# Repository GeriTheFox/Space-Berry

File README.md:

# Space-Berry
 AMD / Xilinx Zynq Ultrascale+ based SBC

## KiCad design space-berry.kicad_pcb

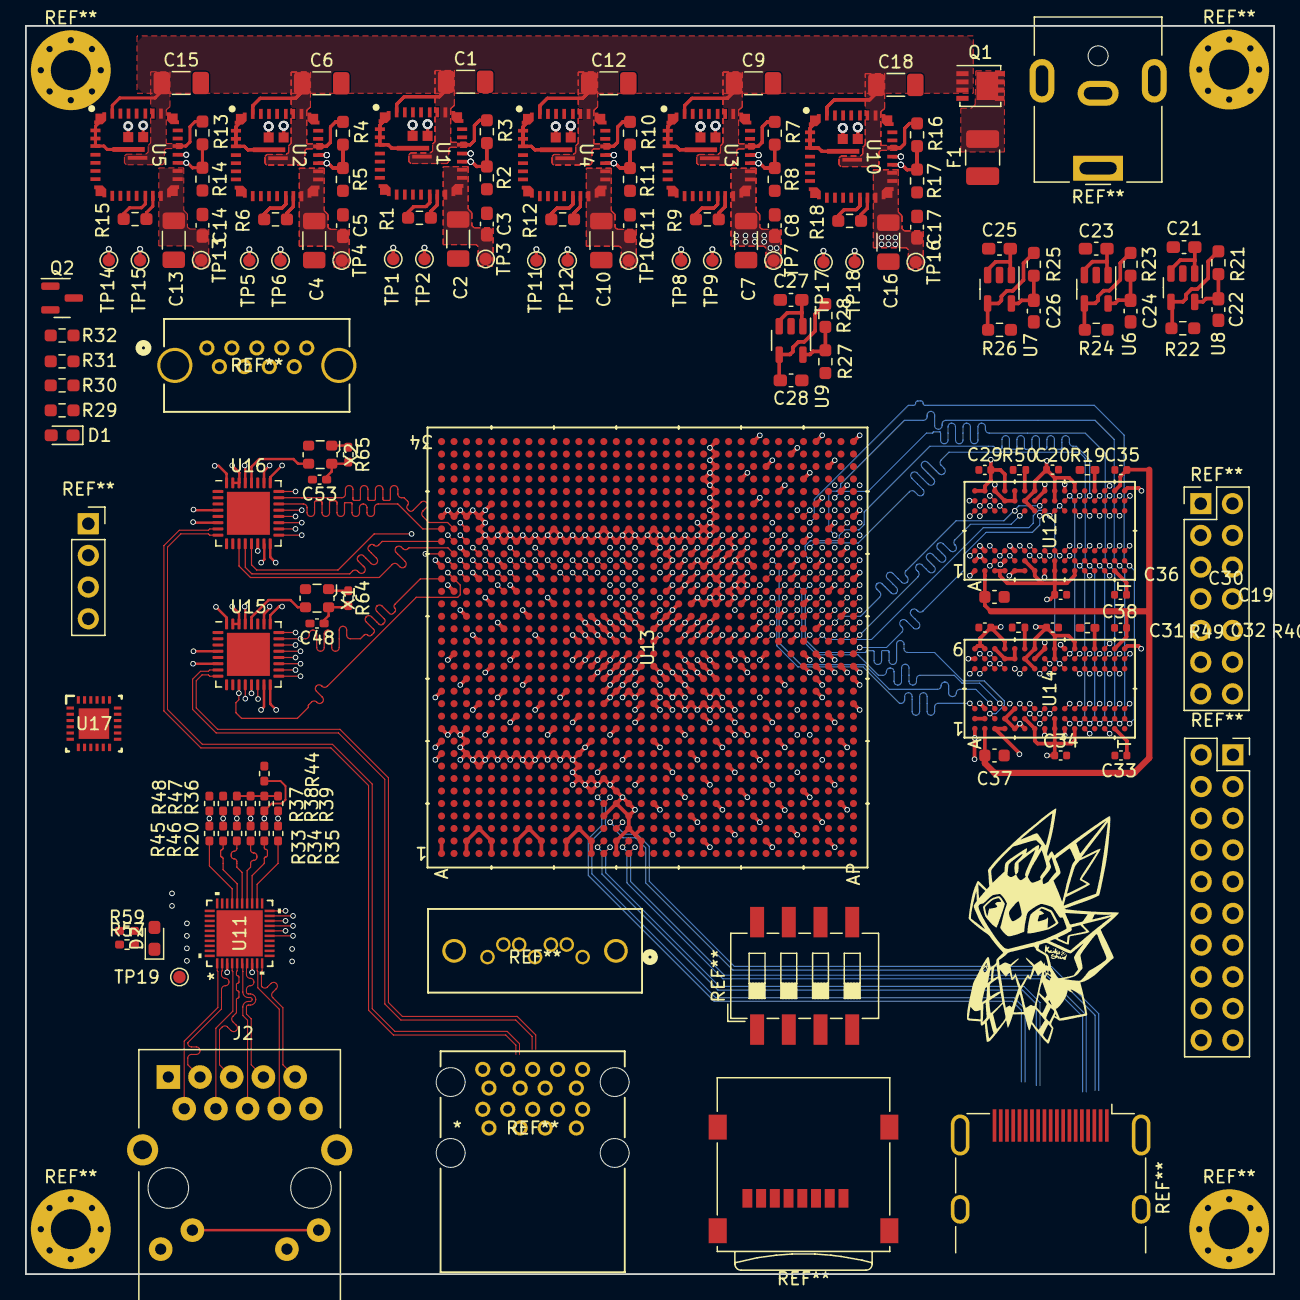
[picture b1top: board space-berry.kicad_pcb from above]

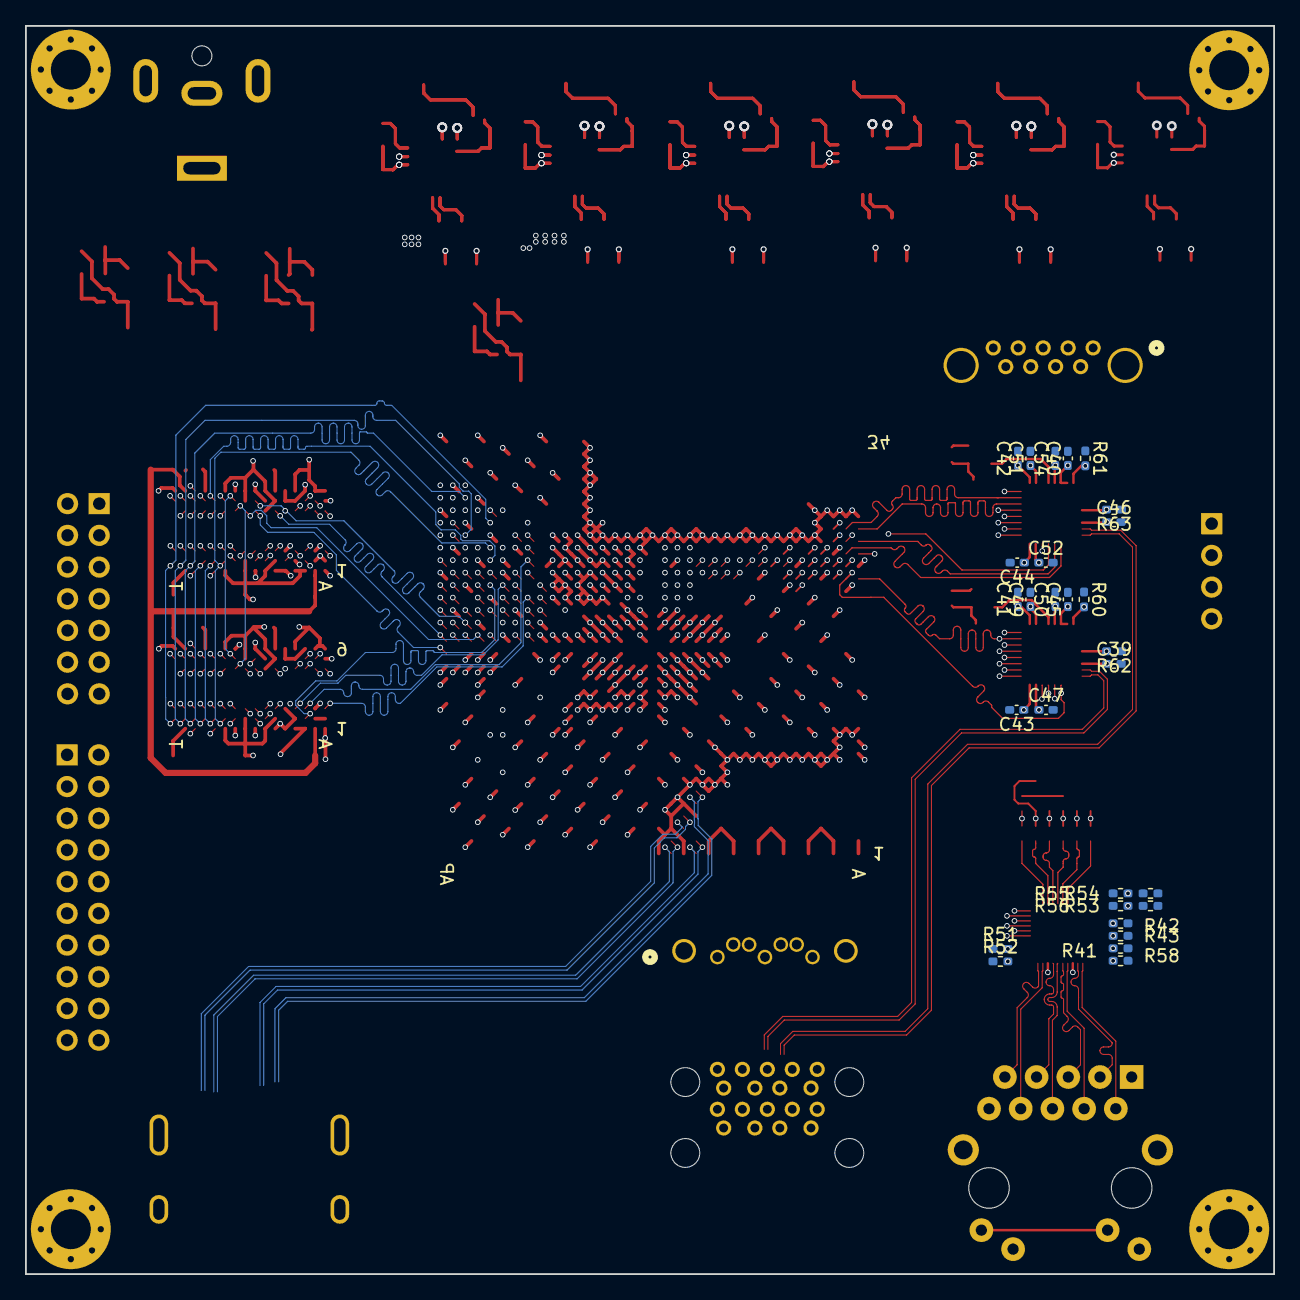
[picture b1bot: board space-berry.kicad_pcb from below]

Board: 8 copper layers, 100.0 x 100.0 mm, 163 parts (28 on the bottom side), 228 nets.

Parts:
C1, C6, C9, C12, C15, C18: 20uF; C_1206_3216Metric_Pad1.33x1.80mm_HandSolder
C2, C4, C7, C10, C13, C16: 44uF; C_1206_3216Metric_Pad1.33x1.80mm_HandSolder
C3, C5, C8, C11, C14, C17: 100nF; C_0603_1608Metric_Pad1.08x0.95mm_HandSolder
C19, C20, C29, C30, C31, C32, C33, C34, C35, C38: 100nF; C_0402_1005Metric
C21, C22, C23, C24, C25, C26, C27, C28: 10uf; C_0603_1608Metric_Pad1.08x0.95mm_HandSolder
C36, C37: 4.7uF; C_0603_1608Metric
C39, C40, C41, C42, C43, C44, C45, C46, C47, C48, C49, C50, C51, C52, C53, C54: 100nF; C_0402_1005Metric_Pad0.74x0.62mm_HandSolder
D1, D2: LED; LED_0603_1608Metric_Pad1.05x0.95mm_HandSolder
F1: Fuse; Fuse_1210_3225Metric_Pad1.42x2.65mm_HandSolder
J2: RJ45_RB1-125B8G1A; RJ45_UDE_RB1-125B8G1A
Q1: SiS415DNT; Vishay_PowerPAK_1212-8_Single
Q2: TSM2302CX; SOT-23
R1, R6, R9, R12, R15, R18: R adj; R_0603_1608Metric_Pad0.98x0.95mm_HandSolder
R2, R5, R8, R11, R14, R17: 20K opt; R_0603_1608Metric_Pad0.98x0.95mm_HandSolder
R3, R4, R7, R10, R13, R16: 1k opt; R_0603_1608Metric_Pad0.98x0.95mm_HandSolder
R19, R40: 499; R_0402_1005Metric_Pad0.72x0.64mm_HandSolder
R20, R33, R34, R35, R41, R42, R43, R45, R46, R51: 22; R_0402_1005Metric_Pad0.72x0.64mm_HandSolder
R21, R22, R23, R24, R25, R26, R27, R28: R; R_0603_1608Metric_Pad0.98x0.95mm_HandSolder
R29: 10; R_0603_1608Metric_Pad0.98x0.95mm_HandSolder
R30, R31, R32: 10K; R_0603_1608Metric_Pad0.98x0.95mm_HandSolder
R36, R37, R38, R39, R52, R55, R56, R59: 4K7; R_0402_1005Metric_Pad0.72x0.64mm_HandSolder
R44, R47, R48: 1K; R_0402_1005Metric_Pad0.72x0.64mm_HandSolder
R49, R50: 240; R_0402_1005Metric
R53, R54, R57: 420; R_0402_1005Metric_Pad0.72x0.64mm_HandSolder
R58: 2K5; R_0402_1005Metric_Pad0.72x0.64mm_HandSolder
R60, R61, R62, R63, R64, R65: R; R_0402_1005Metric_Pad0.72x0.64mm_HandSolder
TP1, TP5, TP8, TP11, TP14, TP17: PG; TestPoint_Pad_D1.0mm
TP2, TP6, TP9, TP12, TP15, TP18: EN; TestPoint_Pad_D1.0mm
TP3, TP4, TP7, TP10, TP13, TP16: Vout; TestPoint_Pad_D1.0mm
TP19: Eth clk; TestPoint_Pad_D1.0mm
U1, U2, U3, U4, U5, U10: NAM12S06-D
U6, U7, U8, U9: TLV75801PDBV; SOT-23-5
U11: RTL8211F-CG; RTL8211F-CG_RTK
U12, U14: K4A8G165WC-BCTD; FBGA96X16_7P5X13P3_SAM
U13: XCZU15EG-2FFVB1156E; FFVB1156_XIL
U15, U16: USB3300-EZK; QFN-32-1EP_5x5mm_P0.5mm_EP3.45x3.45mm
U17: CDCI6214RGET; CDCI6214RGET_NV
X1, X2: ECS-2520MV-xxx-xx; Oscillator_SMD_ECS_2520MV-xxx-xx-4Pin_2.5x2.0mm

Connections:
0V85_LDO: C26.1, R25.1, U7.5 (OUT)
1V2: C7.1, C8.1, C19.1, C20.1, C29.1, C30.1, C31.1, C32.1, C33.1, C34.1, TP7.1, U3.17 (VOUT), U3.18 (VOUT), U3.20 (VOUT), U3.21 (VOUT), U12.A1 (VDDQ), U12.A9 (VDDQ), U12.B3 (VDD), U12.B9 (VDD), U12.C1 (VDDQ), U12.D1 (VDD), U12.D9 (VDDQ), U12.F2 (VDDQ), U12.F8 (VDDQ), U12.G1 (VDDQ), U12.G7 (VDD), U12.G9 (VDDQ), U12.J1 (VDD), U12.J2 (VDDQ), U12.J8 (VDDQ), U12.J9 (VDD), U12.L1 (VDD), U12.L9 (VDD), U12.R1 (VDD), U12.T9 (VDD), U14.A1 (VDDQ), U14.A9 (VDDQ), U14.B3 (VDD), U14.B9 (VDD), U14.C1 (VDDQ), U14.D1 (VDD), U14.D9 (VDDQ), U14.F2 (VDDQ), U14.F8 (VDDQ), U14.G1 (VDDQ), U14.G7 (VDD), U14.G9 (VDDQ), U14.J1 (VDD), U14.J2 (VDDQ), U14.J8 (VDDQ), U14.J9 (VDD), U14.L1 (VDD), U14.L9 (VDD), U14.R1 (VDD), U14.T9 (VDD)
1V2_LDO: C28.1, R27.1, U9.5 (OUT)
1V8: C27.1, C47.1, C48.1, C49.1, C50.1, C51.1, C52.1, C53.1, C54.1, R64.2, R65.2, U9.1 (IN), U9.3 (EN), U15.15 (VDD1.8), U15.26 (VDD1.8), U15.29 (VDDA1.8), U16.15 (VDD1.8), U16.26 (VDD1.8), U16.29 (VDDA1.8), X1.4 (VDD), X2.4 (VDD)
1V8_ETH: R36.1, R37.1, R38.1, R39.1, R52.1
1V8_LDO: C24.1, R23.1, U6.5 (OUT)
2V5_LDO: C22.1, C35.1, C36.1, C37.1, C38.1, R21.1, U8.5 (OUT), U12.B1 (VPP), U12.R9 (VPP), U14.B1 (VPP), U14.R9 (VPP)
3V3: C21.1, C23.1, C25.1, C39.1, C40.1, C41.1, C42.1, C43.1, C44.1, C45.1, C46.1, R55.1, R56.1, U6.1 (IN), U6.3 (EN), U7.1 (IN), U7.3 (EN), U8.1 (IN), U8.3 (EN), U11.11 (AVDD33), U11.40 (AVDD33), U15.6 (VDD3.3), U15.16 (VDD3.3), U15.25 (VDD3.3), U15.30 (VDD3.3), U15.31 (REG_EN), U16.6 (VDD3.3), U16.16 (VDD3.3), U16.25 (VDD3.3), U16.30 (VDD3.3), U16.31 (REG_EN)
3V3_PG: R31.2, R32.2
5V0: R62.1, R63.1
DDR_A0: U12.P3 (A0), U13.AP29 (PS_DDR_A0), U14.P3 (A0)
DDR_A1: U12.P7 (A1), U13.AP30 (PS_DDR_A1), U14.P7 (A1)
DDR_A2: U12.R3 (A2), U13.AP26 (PS_DDR_A2), U14.R3 (A2)
DDR_A3: U12.N7 (A3), U13.AP27 (PS_DDR_A3), U14.N7 (A3)
DDR_A4: U12.N3 (A4), U13.AP25 (PS_DDR_A4), U14.N3 (A4)
DDR_A5: U12.P8 (A5), U13.AN24 (PS_DDR_A5), U14.P8 (A5)
DDR_A6: U12.P2 (A6), U13.AM29 (PS_DDR_A6), U14.P2 (A6)
DDR_A7: U12.R8 (A7), U13.AM28 (PS_DDR_A7), U14.R8 (A7)
DDR_A8: U12.R2 (A8), U13.AM26 (PS_DDR_A8), U14.R2 (A8)
DDR_A9: U12.R7 (A9), U13.AM25 (PS_DDR_A9), U14.R7 (A9)
DDR_A10: U12.M3 (A10/AP), U13.AL28 (PS_DDR_A10), U14.M3 (A10/AP)
DDR_A11: U12.T2 (A11), U13.AK27 (PS_DDR_A11), U14.T2 (A11)
DDR_A12: U12.M7 (A12/BC_n), U13.AJ25 (PS_DDR_A12), U14.M7 (A12/BC_n)
DDR_A13: U12.T8 (A13), U13.AL25 (PS_DDR_A13), U14.T8 (A13)
DDR_A14: U12.L2 (WE_n/A14), U13.AK25 (PS_DDR_A14), U14.L2 (WE_n/A14)
DDR_A15: U12.M8 (CAS_n/A15), U13.AK24 (PS_DDR_A15), U14.M8 (CAS_n/A15)
DDR_A16: U12.L8 (RAS_n), U13.AM24 (PS_DDR_A16), U14.L8 (RAS_n)
DDR_ACT: U12.L3 (ACT_n), U13.AG25 (PS_DDR_ACT_N), U14.L3 (ACT_n)
DDR_ALTER: U12.P9 (ALERT_n), U13.AF22 (PS_DDR_ALERT_N), U14.P9 (ALERT_n)
DDR_BA0: U12.N2 (BA0), U13.AH26 (PS_DDR_BA0), U14.N2 (BA0)
DDR_BA1: U12.N8 (BA1), U13.AG26 (PS_DDR_BA1), U14.N8 (BA1)
DDR_BG0: U12.M2 (BG0), U13.AK28 (PS_DDR_BG0), U14.M2 (BG0)
DDR_BY_L0: U12.G2 (DQL0), U13.AP20 (PS_DDR_DQ0)
DDR_BY_L1: U12.F7 (DQL1), U13.AP18 (PS_DDR_DQ1)
DDR_BY_L2: U12.H3 (DQL2), U13.AP19 (PS_DDR_DQ2)
DDR_BY_L3: U12.H7 (DQL3), U13.AP17 (PS_DDR_DQ3)
DDR_BY_L4: U12.H2 (DQL4), U13.AM20 (PS_DDR_DQ4)
DDR_BY_L5: U12.H8 (DQL5), U13.AM19 (PS_DDR_DQ5)
DDR_BY_L6: U12.J3 (DQL6), U13.AM18 (PS_DDR_DQ6)
DDR_BY_L7: U12.J7 (DQL7), U13.AL18 (PS_DDR_DQ7)
DDR_BY_L16: U13.AL20 (PS_DDR_DQ16), U14.G2 (DQL0)
DDR_BY_L17: U13.AK20 (PS_DDR_DQ17), U14.F7 (DQL1)
DDR_BY_L18: U13.AJ20 (PS_DDR_DQ18), U14.H3 (DQL2)
DDR_BY_L19: U13.AK18 (PS_DDR_DQ19), U14.H7 (DQL3)
DDR_BY_L20: U13.AG20 (PS_DDR_DQ20), U14.H2 (DQL4)
DDR_BY_L21: U13.AH18 (PS_DDR_DQ21), U14.H8 (DQL5)
DDR_BY_L22: U13.AG19 (PS_DDR_DQ22), U14.J3 (DQL6)
DDR_BY_L23: U13.AG18 (PS_DDR_DQ23), U14.J7 (DQL7)
DDR_BY_U8: U12.A3 (DQU0), U13.AP22 (PS_DDR_DQ8)
DDR_BY_U9: U12.B8 (DQU1), U13.AP21 (PS_DDR_DQ9)
DDR_BY_U10: U12.C3 (DQU2), U13.AP24 (PS_DDR_DQ10)
DDR_BY_U11: U12.C7 (DQU3), U13.AN23 (PS_DDR_DQ11)
DDR_BY_U12: U12.C2 (DQU4), U13.AL21 (PS_DDR_DQ12)
DDR_BY_U13: U12.C8 (DQU5), U13.AL22 (PS_DDR_DQ13)
DDR_BY_U14: U12.D3 (DQU6), U13.AM23 (PS_DDR_DQ14)
DDR_BY_U15: U12.D7 (DQU7), U13.AL23 (PS_DDR_DQ15)
DDR_BY_U24: U13.AG21 (PS_DDR_DQ24), U14.A3 (DQU0)
DDR_BY_U25: U13.AH21 (PS_DDR_DQ25), U14.B8 (DQU1)
DDR_BY_U26: U13.AG24 (PS_DDR_DQ26), U14.C3 (DQU2)
DDR_BY_U27: U13.AG23 (PS_DDR_DQ27), U14.C7 (DQU3)
DDR_BY_U28: U13.AK22 (PS_DDR_DQ28), U14.C2 (DQU4)
DDR_BY_U29: U13.AJ21 (PS_DDR_DQ29), U14.C8 (DQU5)
DDR_BY_U30: U13.AJ22 (PS_DDR_DQ30), U14.D3 (DQU6)
DDR_BY_U31: U13.AK23 (PS_DDR_DQ31), U14.D7 (DQU7)
DDR_CK+: U12.K7 (CK_t), U13.AN26 (PS_DDR_CK0), U14.K7 (CK_t)
DDR_CK-: U12.K8 (CK_c), U13.AN27 (PS_DDR_CK_N0), U14.K8 (CK_c)
DDR_CKE: U12.K2 (CKE), U13.AN29 (PS_DDR_CKE0), U14.K2 (CKE)
DDR_CS: U12.L7 (CS_n), U13.AN28 (PS_DDR_CS_N0), U14.L7 (CS_n)
DDR_DM0: U12.E7 (DML_n/DBIL_n), U14.E7 (DML_n/DBIL_n)
DDR_DM1: U12.E2 (DMU_n/DBIU_n), U14.E2 (DMU_n/DBIU_n)
DDR_DQS0+: U12.G3 (DQSL_c), U13.AN18 (PS_DDR_DQS_P0)
DDR_DQS0-: U12.F3 (DQSL_c), U13.AN19 (PS_DDR_DQS_N0)
DDR_DQS1+: U12.B7 (DQSU_t), U13.AN21 (PS_DDR_DQS_P1)
DDR_DQS1-: U12.A7 (DQSU_c), U13.AN22 (PS_DDR_DQS_N1)
DDR_DQS2+: U13.AH19 (PS_DDR_DQS_P2), U14.G3 (DQSL_c)
DDR_DQS2-: U13.AJ19 (PS_DDR_DQS_N2), U14.F3 (DQSL_c)
DDR_DQS3+: U13.AH22 (PS_DDR_DQS_P3), U14.B7 (DQSU_t)
DDR_DQS3-: U13.AH23 (PS_DDR_DQS_N3), U14.A7 (DQSU_c)
DDR_ODT: U12.K3 (ODT), U13.AM30 (PS_DDR_ODT0), U14.K3 (ODT)
DDR_PAR: U12.T3 (PAR), U13.AF20 (PS_DDR_PARITY), U14.T3 (PAR)
DDR_RES: U12.P1 (RESET_n), U13.AF21 (PS_DDR_RAM_RST_N), U14.P1 (RESET_n)
DDR_VREF: U12.M1 (VREFCA), U14.M1 (VREFCA)
ETH_CLK: R41.2, U13.L23 (PS_MIO38)
ETH_LED_G: R54.1, R55.2, U11.32 (LED0/CFG_EXT)
ETH_LED_Y: R53.1, R56.2, U11.33 (LED1/CFG_LDO0)
ETH_RXD0: R20.1, R39.2, U13.K24 (PS_MIO43)
ETH_RXD1: R33.1, R38.2, U13.N24 (PS_MIO44)
ETH_RXD2: R34.1, R37.2, R44.2, U13.P24 (PS_MIO45)
ETH_RXD3: R35.1, R36.2, U13.J25 (PS_MIO46)
ETH_RX_CLK: R46.2, R47.2
ETH_RX_CTL: R45.2, R48.2
ETH_TR1+: J2.R2 (TD1+), U11.1 (MDIP0)
ETH_TR1-: J2.R3 (TD1-), U11.2 (MDIN0)
ETH_TR2+: J2.R4 (TD2+), U11.4 (MDIP1)
ETH_TR2-: J2.R5 (TD2-), U11.5 (MDIN1)
ETH_TR3+: J2.R6 (TD3+), U11.6 (MDIP2)
ETH_TR3-: J2.R7 (TD3-), U11.7 (MDIN2)
ETH_TR4+: J2.R8 (TD4+), U11.9 (MDIP3)
ETH_TR4-: J2.R9 (TD4-), U11.10 (MDIN3)
ETH_TXD0: U11.18 (TXD0), U13.N23 (PS_MIO39)
ETH_TXD1: U11.17 (TXD1), U13.M23 (PS_MIO40)
ETH_TXD2: U11.16 (TXD2), U13.J24 (PS_MIO41)
ETH_TXD3: U11.15 (TXD3), U13.M24 (PS_MIO42)
GND: C1.2, C2.2, C3.2, C4.2, C5.2, C6.2, C7.2, C8.2, C9.2, C10.2, C11.2, C12.2, C13.2, C14.2, C15.2, C16.2, C17.2, C18.2, C19.2, C20.2, C21.2, C22.2, C23.2, C24.2, C25.2, C26.2, C27.2, C28.2, C29.2, C30.2, C31.2, C32.2, C33.2, C34.2, C35.2, C36.2, C37.2, C38.2, C39.2, C40.2, C41.2, C42.2, C43.2, C44.2, C45.2, C46.2, C47.2, C48.2, C49.2, C50.2, C51.2, C52.2, C53.2, C54.2, Q1.4 (G), Q2.2 (S), R2.1, R5.1, R8.1, R11.1, R14.1, R17.1, R19.1, R22.2, R24.2, R26.2, R28.2, R40.1, R43.2, R44.1, R47.1, R48.1, R49.1, R50.1, R57.1, R58.2, R59.2, R60.1, R61.1, U1.11 (AGND), U1.31 (PGND), U1.32 (PGND), U1.33 (PGND), U1.34 (PGND), U1.37 (PGND), U1.38 (PGND), U2.11 (AGND), U2.31 (PGND), U2.32 (PGND), U2.33 (PGND), U2.34 (PGND), U2.37 (PGND), U2.38 (PGND), U3.11 (AGND), U3.31 (PGND), U3.32 (PGND), U3.33 (PGND), U3.34 (PGND), U3.37 (PGND), U3.38 (PGND), U4.11 (AGND), U4.31 (PGND), U4.32 (PGND), U4.33 (PGND), U4.34 (PGND), U4.37 (PGND), U4.38 (PGND), U5.11 (AGND), U5.31 (PGND), U5.32 (PGND), U5.33 (PGND), U5.34 (PGND), U5.37 (PGND), U5.38 (PGND), U6.2 (GND), U7.2 (GND), U8.2 (GND), U9.2 (GND), U10.11 (AGND), U10.31 (PGND), U10.32 (PGND), U10.33 (PGND), U10.34 (PGND), U10.37 (PGND), U10.38 (PGND), U11.41 (GND), U12.A2 (VSSQ), U12.A8 (VSSQ), U12.B2 (VSS), U12.C9 (VSSQ), U12.D2 (VSSQ), U12.D8 (VSSQ), U12.E1 (VSS), U12.E3 (VSSQ), U12.E8 (VSSQ), U12.E9 (VSS), U12.F1 (VSSQ), U12.G8 (VSS), U12.H1 (VSSQ), U12.H9 (VSSQ), U12.K1 (VSS), U12.K9 (VSS), U12.M9 (VSS), U12.N1 (VSS), U12.T1 (VSS), U13.A11 (GND), U13.A14 (GND), U13.A19 (GND), U13.A24 (GND), U13.A28 (GND), U13.A33 (GND), U13.A34 (GND), U13.AA4 (GND), U13.AA14 (GND), U13.AA16 (GND), U13.AA18 (GND), U13.AA20 (GND), U13.AA24 (GND), U13.AA26 (GND), U13.AA30 (GND), U13.AA33 (GND), U13.AA34 (GND), U13.AB2 (GND), U13.AB7 (GND), U13.AB12 (GND), U13.AB15 (GND), U13.AB17 (GND), U13.AB19 (GND), U13.AB22 (GND), U13.AB24 (GND_PSADC), U13.AB26 (GND), U13.AB27 (GND), U13.AB31 (GND), U13.AC5 (GND), U13.AC10 (GND), U13.AC16 (GND), U13.AC18 (GND), U13.AC20 (GND), U13.AC25 (GND_PSADC), U13.AC27 (GND), U13.AC28 (GND), U13.AC29 (GND), U13.AC30 (GND), U13.AC31 (GND), U13.AC32 (GND), U13.AC33 (GND), U13.AC34 (GND), U13.AD3 (GND), U13.AD13 (GND), U13.AD23 (GND), U13.AE6 (GND), U13.AE11 (GND), U13.AE21 (GND), U13.AE26 (GND), U13.AE31 (GND), U13.AF4 (GND), U13.AF19 (GND), U13.AF24 (GND), U13.AF29 (GND), U13.AF34 (GND), U13.AG2 (GND), U13.AG12 (GND), U13.AG22 (GND), U13.AG32 (GND), U13.AH5 (GND), U13.AH10 (GND), U13.AH15 (GND), U13.AH20 (GND), U13.AH25 (GND), U13.AH30 (GND), U13.AJ3 (GND), U13.AJ18 (GND), U13.AJ23 (GND), U13.AJ33 (GND), U13.AK6 (GND), U13.AK21 (GND), U13.AK26 (GND), U13.AK31 (GND), U13.AL4 (GND), U13.AL14 (GND), U13.AL19 (GND), U13.AL34 (GND), U13.AM2 (GND), U13.AM7 (GND), U13.AM12 (GND), U13.AM17 (GND), U13.AM22 (GND), U13.AM27 (GND), U13.AM32 (GND), U13.AN5 (GND), U13.AN10 (GND), U13.AN15 (GND), U13.AN20 (GND), U13.AP13 (GND), U13.AP23 (GND), U13.AP28 (GND), U13.AP34 (GND), U13.B7 (GND), U13.B11 (GND), U13.B17 (GND), U13.B22 (GND), U13.B28 (GND), U13.B32 (GND), U13.C1 (GND), U13.C2 (GND), U13.C5 (GND), U13.C9 (GND), U13.C10 (GND), U13.C11 (GND), U13.C15 (GND), U13.C20 (GND), U13.C25 (GND), U13.C28 (GND), U13.C30 (GND), U13.C33 (GND), U13.C34 (GND), U13.D3 (GND), U13.D8 (GND), U13.D9 (GND), U13.D13 (GND), U13.D18 (GND), U13.D26 (GND), U13.D27 (GND), U13.D28 (GND), U13.D31 (GND), U13.E1 (GND), U13.E2 (GND), U13.E6 (GND), U13.E9 (GND), U13.E11 (GND), U13.E26 (GND), U13.E29 (GND), U13.E33 (GND), U13.E34 (GND), U13.F4 (GND), U13.F7 (GND), U13.F9 (GND), U13.F19 (GND), U13.F26 (GND), U13.F27 (GND), U13.F32 (GND), U13.G1 (GND), U13.G2 (GND), U13.G5 (GND), U13.G9 (GND), U13.G26 (GND), U13.G30 (GND), U13.G33 (GND), U13.G34 (GND), U13.H3 (GND), U13.H8 (GND), U13.H9 (GND), U13.H15 (GND), U13.H26 (GND), U13.H28 (GND), U13.H31 (GND), U13.J1 (GND), U13.J2 (GND), U13.J6 (GND), U13.J9 (GND), U13.J23 (GND), U13.J26 (GND), U13.J29 (GND), U13.J33 (GND), U13.J34 (GND), U13.K4 (GND), U13.K7 (GND), U13.K9 (GND), U13.K11 (GND), U13.K21 (GND), U13.K26 (GND), U13.K27 (GND), U13.K32 (GND), U13.L1 (GND), U13.L2 (GND), U13.L5 (GND), U13.L9 (GND), U13.L14 (GND), U13.L26 (GND), U13.L30 (GND), U13.L33 (GND), U13.L34 (GND), U13.M3 (GND), U13.M7 (GND), U13.M8 (GND), U13.M9 (GND), U13.M12 (GND), U13.M17 (GND), U13.M19 (GND), U13.M26 (GND), U13.M28 (GND), U13.M31 (GND), U13.N1 (GND), U13.N2 (GND), U13.N6 (GND), U13.N7 (GND), U13.N10 (GND), U13.N16 (GND), U13.N18 (GND), U13.N20 (GND), U13.N26 (GND), U13.N29 (GND), U13.N33 (GND), U13.N34 (GND), U13.P4 (GND), U13.P7 (GND), U13.P13 (GND), U13.P15 (GND), U13.P17 (GND), U13.P19 (GND), U13.P23 (GND), U13.P26 (GND), U13.P27 (GND), U13.P32 (GND), U13.R1 (GND), U13.R2 (GND), U13.R5 (GND), U13.R6 (GND), U13.R7 (GND), U13.R11 (GND), U13.R14 (GND), U13.R16 (GND), U13.R18 (GND), U13.R20 (GND), U13.R26 (GND), U13.R30 (GND), U13.R33 (GND), U13.R34 (GND), U13.T3 (GND), U13.T4 (GND), U13.T5 (GND), U13.T15 (GND), U13.T17 (GNDADC), U13.T19 (GND), U13.T26 (GND), U13.T27 (GND), U13.T28 (GND), U13.T31 (GND), U13.T32 (GND), U13.U1 (GND), U13.U2 (GND), U13.U3 (GND), U13.U12 (GND), U13.U16 (GND), U13.U20 (GND), U13.U26 (GND), U13.U29 (GND), U13.U30 (GND), U13.U33 (GND), U13.U34 (GND), U13.V5 (GND), U13.V10 (GND), U13.V15 (GND), U13.V19 (GND), U13.V25 (GND), U13.V26 (GND), U13.V27 (GND), U13.V31 (GND), U13.W3 (GND), U13.W13 (GND), U13.W16 (GND), U13.W20 (GND), U13.W23 (GND), U13.W26 (GND), U13.W29 (GND), U13.W33 (GND), U13.W34 (GND), U13.Y6 (GND), U13.Y15 (GND), U13.Y17 (GND), U13.Y19 (GND), U13.Y21 (GND), U13.Y26 (GND), U13.Y28 (GND), U13.Y32 (GND), U14.A2 (VSSQ), U14.A8 (VSSQ), U14.B2 (VSS), U14.C9 (VSSQ), U14.D2 (VSSQ), U14.D8 (VSSQ), U14.E1 (VSS), U14.E3 (VSSQ), U14.E8 (VSSQ), U14.E9 (VSS), U14.F1 (VSSQ), U14.G8 (VSS), U14.H1 (VSSQ), U14.H9 (VSSQ), U14.K1 (VSS), U14.K9 (VSS), U14.M9 (VSS), U14.N1 (VSS), U14.T1 (VSS), U15.1 (GND), U15.2 (GND), U15.33 (GND), U16.1 (GND), U16.2 (GND), U16.33 (GND), X1.2 (GND), X2.2 (GND)
unnamed: C2.1, C3.1, TP3.1, U1.17 (VOUT), U1.18 (VOUT), U1.20 (VOUT), U1.21 (VOUT)
unnamed: C4.1, C5.1, TP4.1, U2.17 (VOUT), U2.18 (VOUT), U2.20 (VOUT), U2.21 (VOUT)
unnamed: C10.1, C11.1, TP10.1, U4.17 (VOUT), U4.18 (VOUT), U4.20 (VOUT), U4.21 (VOUT)
unnamed: C13.1, C14.1, TP13.1, U5.17 (VOUT), U5.18 (VOUT), U5.20 (VOUT), U5.21 (VOUT)
unnamed: C16.1, C17.1, TP16.1, U10.17 (VOUT), U10.18 (VOUT), U10.20 (VOUT), U10.21 (VOUT)
unnamed: D1.1 (K), R30.2
unnamed: D2.2 (A), R59.1, U11.34 (LED2/CFG_LDO1)
unnamed: D2.1 (K), R57.2
unnamed: J2.R10 (GND), J2.SH
unnamed: J2.L1, J2.L3
unnamed: J2.L2, R53.2
unnamed: J2.L4, R54.2
unnamed: F1.2, Q1.5 (D)
unnamed: Q2.3 (D), R30.1
unnamed: Q2.1 (G), R31.1
unnamed: R42.2, TP19.1
unnamed: R2.2, R3.1, TP2.1, U1.22 (EN)
unnamed: R1.1, U1.16 (FB)
unnamed: TP1.1, U1.23 (PG)
unnamed: R1.2, U1.15 (RGND)
unnamed: U1.1 (SW), U1.2 (SW), U1.3 (SW), U1.4 (SW), U1.39 (SW)
unnamed: R4.1, R5.2, TP6.1, U2.22 (EN)
unnamed: R6.1, U2.16 (FB)
unnamed: TP5.1, U2.23 (PG)
unnamed: R6.2, U2.15 (RGND)
unnamed: U2.1 (SW), U2.2 (SW), U2.3 (SW), U2.4 (SW), U2.39 (SW)
unnamed: R7.1, R8.2, TP9.1, U3.22 (EN)
unnamed: R9.1, U3.16 (FB)
unnamed: TP8.1, U3.23 (PG)
unnamed: R9.2, U3.15 (RGND)
unnamed: U3.1 (SW), U3.2 (SW), U3.3 (SW), U3.4 (SW), U3.39 (SW)
unnamed: R10.1, R11.2, TP12.1, U4.22 (EN)
unnamed: R12.1, U4.16 (FB)
unnamed: TP11.1, U4.23 (PG)
unnamed: R12.2, U4.15 (RGND)
unnamed: U4.1 (SW), U4.2 (SW), U4.3 (SW), U4.4 (SW), U4.39 (SW)
unnamed: R13.1, R14.2, TP15.1, U5.22 (EN)
unnamed: R15.1, U5.16 (FB)
unnamed: TP14.1, U5.23 (PG)
unnamed: R15.2, U5.15 (RGND)
unnamed: U5.1 (SW), U5.2 (SW), U5.3 (SW), U5.4 (SW), U5.39 (SW)
unnamed: R23.2, R24.1, U6.4 (FB)
unnamed: R25.2, R26.1, U7.4 (FB)
unnamed: R21.2, R22.1, U8.4 (FB)
unnamed: R27.2, R28.1, U9.4 (FB)
unnamed: R16.1, R17.2, TP18.1, U10.22 (EN)
unnamed: R18.1, U10.16 (FB)
unnamed: TP17.1, U10.23 (PG)
unnamed: R18.2, U10.15 (RGND)
unnamed: U10.1 (SW), U10.2 (SW), U10.3 (SW), U10.4 (SW), U10.39 (SW)
unnamed: R42.1, U11.35 (CLKOUT)
unnamed: R51.2, R52.2, U11.12 (PHYRSTB)
unnamed: R58.1, U11.39 (RSET)
unnamed: R46.1, U11.26 (RXCTL/PHYAD2)
unnamed: R45.1, U11.27 (RXC/PHYAD1)
unnamed: R20.2, U11.25 (RXD0/RXDLY)
unnamed: R33.2, U11.24 (RXD1/TXDLY)
unnamed: R34.2, U11.23 (RXD2/PLLOFF)
unnamed: R35.2, U11.22 (RXD3/PHYAD0)
unnamed: R43.1, U11.36 (XTAL_IN)
unnamed: R41.1, U11.37 (XTAL_OUT/EXT_CLK)
unnamed: U11.3 (AVDD10), U11.8 (AVDD10), U11.38 (AVDD10)
unnamed: R19.2, U12.N9 (TEN)
unnamed: R50.2, U12.F9 (ZQ)
unnamed: U13.F28 (MGTAVCC_L), U13.G29 (MGTAVCC_L), U13.H27 (MGTAVCC_L), U13.L29 (MGTAVCC_L), U13.P28 (MGTAVCC_L), U13.R29 (MGTAVCC_L)
unnamed: U13.A10 (MGTAVCC_R), U13.B8 (MGTAVCC_R), U13.C6 (MGTAVCC_R), U13.D7 (MGTAVCC_R), U13.E5 (MGTAVCC_R), U13.G6 (MGTAVCC_R), U13.K8 (MGTAVCC_R)
unnamed: U13.B31 (MGTAVTT_L), U13.C29 (MGTAVTT_L), U13.D32 (MGTAVTT_L), U13.E30 (MGTAVTT_L), U13.F31 (MGTAVTT_L), U13.H32 (MGTAVTT_L), U13.J30 (MGTAVTT_L), U13.K31 (MGTAVTT_L), U13.M32 (MGTAVTT_L), U13.N30 (MGTAVTT_L), U13.P31 (MGTAVTT_L)
unnamed: U13.B3 (MGTAVTT_R), U13.D4 (MGTAVTT_R), U13.F3 (MGTAVTT_R), U13.H4 (MGTAVTT_R), U13.J5 (MGTAVTT_R), U13.K3 (MGTAVTT_R), U13.L6 (MGTAVTT_R), U13.M4 (MGTAVTT_R), U13.N5 (MGTAVTT_R), U13.P3 (MGTAVTT_R)
unnamed: U13.K28 (MGTVCCAUX_L), U13.M27 (MGTVCCAUX_L)
unnamed: U13.F8 (MGTVCCAUX_R), U13.H7 (MGTVCCAUX_R)
unnamed: U13.AA29 (PS_MGTRAVCC), U13.V28 (PS_MGTRAVCC), U13.W30 (PS_MGTRAVCC), U13.Y27 (PS_MGTRAVCC)
unnamed: U13.AB32 (PS_MGTRAVTT), U13.V32 (PS_MGTRAVTT), U13.Y31 (PS_MGTRAVTT)
unnamed: U13.T14 (VCCAUX), U13.U14 (VCCAUX)
unnamed: U13.U13 (VCCAUX_IO), U13.V13 (VCCAUX_IO), U13.V14 (VCCAUX_IO)
unnamed: U13.AB14 (VCCBRAM), U13.AC14 (VCCBRAM), U13.W14 (VCCBRAM), U13.Y14 (VCCBRAM)
unnamed: U13.AA23 (VCC_PSAUX), U13.AA25 (VCC_PSAUX), U13.AB25 (VCC_PSADC), U13.AC26 (VCC_PSADC), U13.Y22 (VCC_PSAUX), U13.Y23 (VCC_PSAUX)
unnamed: U13.Y24 (VCC_PSDDR_PLL), U13.Y25 (VCC_PSDDR_PLL)
unnamed: U13.AC24 (VCC_PSINTFP), U13.AD21 (VCC_PSINTFP), U13.AD22 (VCC_PSINTFP), U13.AD25 (VCC_PSINTFP), U13.AD26 (VCC_PSINTFP), U13.AE22 (VCC_PSINTFP), U13.AE23 (VCC_PSINTFP)
unnamed: U13.AD24 (VCC_PSINTFP_DDR), U13.AE24 (VCC_PSINTFP_DDR), U13.AE25 (VCC_PSINTFP_DDR)
unnamed: U13.AA21 (VCC_PSINTLP), U13.AB21 (VCC_PSINTLP), U13.AB23 (VCC_PSINTLP), U13.AC21 (VCC_PSINTLP), U13.AC22 (VCC_PSINTLP), U13.AC23 (VCC_PSINTLP)
unnamed: U13.W22 (VCC_PSPLL), U13.W24 (VCC_PSPLL), U13.W25 (VCC_PSPLL)
unnamed: U13.AA13 (VCCINT_IO), U13.AB13 (VCCINT_IO), U13.AC13 (VCCINT_IO), U13.Y13 (VCCINT_IO)
unnamed: U13.A1 (GND), U13.A2 (GND), U13.A9 (GND), U13.B4 (GND)
unnamed: U13.AG27 (VCCO_PSDDR_504), U13.AJ24 (VCCO_PSDDR_504), U13.AJ28 (VCCO_PSDDR_504), U13.AL24 (VCCO_PSDDR_504), U13.AL29 (VCCO_PSDDR_504), U13.AN25 (VCCO_PSDDR_504), U13.AN30 (VCCO_PSDDR_504)
unnamed: U13.AE16 (VCCO_PSIO0_500), U13.AG17 (VCCO_PSIO0_500), U13.AK16 (VCCO_PSIO0_500)
unnamed: U13.L24 (VCCO_PSIO1_501), U13.M22 (VCCO_PSIO1_501)
unnamed: U13.D23 (VCCO_PSIO2_502), U13.F24 (VCCO_PSIO2_502), U13.G22 (VCCO_PSIO2_502)
unnamed: U13.T24 (VCCO_PSIO3_503), U13.U22 (VCCO_PSIO3_503)
unnamed: R40.2, U14.N9 (TEN)
unnamed: R49.2, U14.F9 (ZQ)
unnamed: R60.2, U15.32 (RBIAS)
unnamed: R62.2, U15.4 (VBUS)
unnamed: U15.28 (XI), X1.3 (OUT)
unnamed: R61.2, U16.32 (RBIAS)
unnamed: R63.2, U16.4 (VBUS)
unnamed: U16.28 (XI), X2.3 (OUT)
unnamed: R64.1, X1.1 (Tri-State)
unnamed: R65.1, X2.1 (Tri-State)
USB0_DATA_0: U13.C23 (PS_MIO56), U15.24 (DATA0)
USB0_DATA_1: U13.A23 (PS_MIO57), U15.23 (DATA1)
USB0_DATA_2: U13.F23 (PS_MIO54), U15.22 (DATA2)
USB0_DATA_3: U13.B24 (PS_MIO59), U15.21 (DATA3)
USB0_DATA_4: U13.E24 (PS_MIO60), U15.20 (DATA4)
USB0_DATA_5: U13.C24 (PS_MIO61), U15.19 (DATA5)
USB0_DATA_6: U13.G24 (PS_MIO62), U15.18 (DATA6)
USB0_DATA_8: U13.D24 (PS_MIO63), U15.17 (DATA7)
USB0_DATA_CLK_O: U13.F22 (PS_MIO52), U15.14 (CLKOUT)
USB0_DATA_DIR: U13.E23 (PS_MIO53), U15.12 (DIR)
USB0_DATA_NXT: U13.B23 (PS_MIO55), U15.11 (NXT)
USB0_DATA_STP: U13.G23 (PS_MIO58), U15.13 (STP)
USB1_DATA_0: U13.B26 (PS_MIO68), U16.24 (DATA0)
USB1_DATA_1: U13.B27 (PS_MIO69), U16.23 (DATA1)
USB1_DATA_2: U13.A27 (PS_MIO66), U16.22 (DATA2)
USB1_DATA_3: U13.C27 (PS_MIO71), U16.21 (DATA3)
USB1_DATA_4: U13.E25 (PS_MIO72), U16.20 (DATA4)
USB1_DATA_5: U13.H24 (PS_MIO73), U16.19 (DATA5)
USB1_DATA_6: U13.G25 (PS_MIO74), U16.18 (DATA6)
USB1_DATA_8: U13.D25 (PS_MIO75), U16.17 (DATA7)
USB1_DATA_CLK_O: U13.A25 (PS_MIO64), U16.14 (CLKOUT)
USB1_DATA_DIR: U13.A26 (PS_MIO65), U16.12 (DIR)
USB1_DATA_NXT: U13.B25 (PS_MIO67), U16.11 (NXT)
USB1_DATA_STP: U13.C26 (PS_MIO70), U16.13 (STP)
VCC: C1.1, C6.1, C9.1, C12.1, C15.1, C18.1, D1.2 (A), Q1.1 (S), Q1.2 (S), Q1.3 (S), R3.2, R4.2, R7.2, R10.2, R13.2, R16.2, R29.2, U1.24 (VIN), U1.29 (VIN), U1.35 (VCC), U1.40 (VIN), U2.24 (VIN), U2.29 (VIN), U2.35 (VCC), U2.40 (VIN), U3.24 (VIN), U3.29 (VIN), U3.35 (VCC), U3.40 (VIN), U4.24 (VIN), U4.29 (VIN), U4.35 (VCC), U4.40 (VIN), U5.24 (VIN), U5.29 (VIN), U5.35 (VCC), U5.40 (VIN), U10.24 (VIN), U10.29 (VIN), U10.35 (VCC), U10.40 (VIN)
VCC_INT: U13.AA15 (VCCINT), U13.AA17 (VCCINT), U13.AA19 (VCCINT), U13.AB16 (VCCINT), U13.AB18 (VCCINT), U13.AB20 (VCCINT), U13.AC15 (VCCINT), U13.AC17 (VCCINT), U13.AC19 (VCCINT), U13.M16 (VCCINT), U13.M18 (VCCINT), U13.M20 (VCCINT), U13.N15 (VCCINT), U13.N17 (VCCINT), U13.N19 (VCCINT), U13.P14 (VCCINT), U13.P16 (VCCINT), U13.P18 (VCCINT), U13.P20 (VCCINT), U13.R15 (VCCINT), U13.R17 (VCCINT), U13.R19 (VCCINT), U13.T16 (VCCINT), U13.T20 (VCCINT), U13.U15 (VCCINT), U13.U19 (VCCINT), U13.V16 (VCCINT), U13.V20 (VCCINT), U13.W15 (VCCINT), U13.W19 (VCCINT), U13.Y16 (VCCINT), U13.Y18 (VCCINT), U13.Y20 (VCCINT)

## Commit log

2023-08-17 power supply
    All the overkill converter
2023-08-18 layout plan
2023-08-20 DDR4 added
2023-08-22 Stuff
2023-08-23 DDR4 data lines
2023-08-23 DDR4 finish
2023-08-24 Gbe routing
2023-09-11 usb and stuff
